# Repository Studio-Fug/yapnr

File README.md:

<p align="center">
  <picture>
    <source media="(prefers-color-scheme: dark)" srcset="branding/yapnr-logo-light.png">
    
  </picture>
</p>

<p align="center">

  <!-- Enable once the first public image (after the GHCR visibility switch) and the first
  release (v0.1.0) exist; see docs/releases.md.

  -->

</p>

# yapnr

**Yet another place and route** engine for printed circuit boards.

_The 555 flasher (a TLC555 astable blinker, 10 parts, 2 layers) from the
[regression ladder](docs/regression-ladder.md): from unplaced footprints to 100 % routed, with the
placement starts and routes it was chosen from, then the gloss pass (the copper it replaces in
red, its new copper in green), ending on KiCad's clean DRC verdict. Recorded with the opt-in
[compact placement](docs/design/compact-placement.md) and [gloss](docs/design/gloss.md)
(`PNR_COMPACT=1`, `PNR_GLOSS=1`; both off by default)._

_Left: LEDs placed freely. Right: the same chaser with its LEDs held in a
[line group](docs/constraints-and-hierarchy.md); compact placement keeps each LED's series resistor
flush beside it, and the placer moves and turns the whole row. Both with compact placement and
gloss, as above._

yapnr places components and routes copper for KiCad boards. It uses a mechanical,
Monte-Carlo-driven search: hierarchical block synthesis, power-first placement, native KiCad
routing and DRC in the loop, and electrical contracts (current, pairs, plane access) declared
next to the design.

The engine is being migrated here from the [Splanc](https://github.com/fughilli/splanc) repository,
where it was developed to lay out the Splanc Mini board. The migration plan and progress are in
[`docs/`](docs/index.md) and [`WORKLOG.md`](WORKLOG.md).
The papers and open-source projects it builds on are listed in
[Foundations and references](docs/references.md).

## Status

Alpha: this repository holds the build, CI and documentation scaffolding, a command-line stub, the
[migration plan](docs/migration-plan.md), and the engine imported from Splanc at its original
paths under `hardware/`: its committed history and its newer, uncommitted state
([manifest](docs/history/import-manifest.md)). The package restructuring follows. KiCad 10 only.

## Quick start

With [Bazelisk](https://github.com/bazelbuild/bazelisk) installed as `bazel`:

```sh
bazel run //:yapnr -- --version   # the CLI
bazel run //:doctor               # environment report
bazel test //...                  # unit tests and repository checks
bazel run //docs:build            # documentation -> docs/site/html/
```

See [DEVELOPERS.md](DEVELOPERS.md) for setup (including the headless KiCad copy on macOS) and
[CONTRIBUTING.md](CONTRIBUTING.md) for the contribution policy.

## Container image

`ghcr.io/studio-fug/yapnr` bundles KiCad 10, CPython 3.11 with CPU-only torch, and yapnr, for
linux/amd64 and linux/arm64, so running yapnr needs Docker and nothing else:

```sh
docker run --rm ghcr.io/studio-fug/yapnr:edge doctor
```

`edge` follows `main`; release tags (`X.Y.Z`, `X.Y`, `latest`) start with v0.1.0. See
[docs/containers.md](docs/containers.md) for projects, UID mapping, resource limits and Apple
Silicon, and [docs/releases.md](docs/releases.md) for versioning and releases.

## License

Copyright (C) 2026 Kevin Balke. Licensed under the GNU Affero General Public License v3.0 or later
(`AGPL-3.0-or-later`); see [LICENSE](LICENSE). Third-party material is listed in
[THIRD_PARTY.md](THIRD_PARTY.md).

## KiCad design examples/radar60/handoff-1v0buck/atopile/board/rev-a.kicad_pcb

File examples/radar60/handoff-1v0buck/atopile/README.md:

# atopile board, ERC-equivalent report, and pin mapping

Added at the request of the agent receiving this handoff: "please include the original
atopile-generated board/netlist, its schematic/ERC check report, and the symbolic-to-numeric
IC pin mapping. The current schematic checker misreads the integrated KiCad 10 board, so
those will let me verify connectivity independently." The rest of the handoff (routed boards,
documents, simulations, manifest) is described in
`../README.md`.

## `board/` -- the original atopile-generated board (parts unplaced, unrouted)

atopile writes no KiCad schematic; `rev-a.kicad_pcb` **is** the netlist (every footprint pad
carries its net name) and is the pre-place/pre-route ground truth the router's seed and every
`candidate.kicad_pcb` descend from.

- `rev-a.kicad_pcb` -- the build output (atopile 0.15.8, KiCad CLI 10.0.6; see `result.json`).
  No zone fills, 520 KB uncompressed, committed as-is.
- `ato.log` -- the full atopile build log for this output (build-design, BOM, variable-report,
  power-tree, pinout targets).
- `result.json`, `catalog.json` -- build manifest and parts catalog atopile wrote alongside the
  board, including the sha256 of every output file atopile produced (`result.json.sha256`).
- `rev-a.bom.csv` / `rev-a.bom.json` -- bill of materials (manufacturer, MPN, LCSC part #).
- `power_tree.md`, `rev-a.power_tree.ato.json`, `rev-a.variables.ato.json` -- atopile's own
  power-tree and parameter reports for this build.
- `hook.jsonl` -- atopile's module-patch trace for this run (diagnostic only).

## `pinout/` -- the symbolic-to-numeric IC pin mapping

One JSON file per fitted part (atopile's `pinout` build target), each giving, per lead:
`leadDesignator` (the symbolic pin/ball name atopile's source uses), `padNumbers` (the numeric
KiCad pad number(s) that lead maps to), `netName` (the net on `rev-a.kicad_pcb`), and
`isConnected`. This is the authoritative symbolic<->numeric bridge for every IC on the board,
including:

- U1 (`155_radio_u1.json`, IWR6843) -- 161 leads against the ABL0161 ball map.
- U2 (`086_pmic_u2.json`, LP87524J) -- 27 leads.
- U3 (`023_flash_u3.json`) -- 9 leads.
- U4 (`013_can_u4.json`) -- 9 leads.
- U5 (`093_power_in_efuse.json`, TPS259474) -- 10 leads.
- J2 (`014_debug_j2.json`) -- 36 leads.
- Every other fitted part (passives, test points, connectors, mounting holes): one file each,
  180 files total.

The companion ball map the radar flow's own checker uses for U1 is
`examples/radar60/schematic/tools/data/abl0161_ballmap.json` (already on this branch; not
duplicated here).

## `erc/` -- the ERC-equivalent check and the reproduced "misreads KiCad 10" symptom

atopile emits no schematic, so there is no KiCad ERC to run. The radar flow's own
ERC-equivalent is `examples/radar60/schematic/tools/check_schematic.py` (already on this
branch), which re-derives pin-table, power, conflict, annotation and quantified-warning checks
directly from a built/placed/routed `.kicad_pcb`'s netlist. Its own docstring states the checks
it runs; see that file for the full list.

Both reports here were produced by running that exact script, unmodified, against two boards:

- `check-atopile-board.json` -- run against `board/rev-a.kicad_pcb` (parts unplaced).
  **64 errors**, all `"<ref> (<atopile address>) pad <N> (<N>): no pin type in the check
table"`, confined to U2 (pmic.u2), U3 (flash.u3), U4 (can.u4) and U5 (power_in.efuse).
- `check-routed-s1-board.json` -- run against
  `~/yapnr-runs/fetched/20261006-mceval-5818f8/tasks/mc~s1/result/out/s1/files/candidate.kicad_pcb`
  (the routed seed s1 board; see `../results/s1`). **573 errors**: the same 64, repeated, plus
  one additional `"net : 14 push-pull outputs [...]"` error naming 14 distinct U1 pins
  (SPIB_CS_N, LVDS_TXP/M[0:1], LVDS_CLKP/M, LVDS_FRCLKP/M, RS232_TX, MCU_CLKOUT, QSPI_CS_N,
  SPI_HOST_INTR, QSPI_CLK) as if they all sat on one net literally named `""` (empty).

### The symptom, reproduced and root-caused

This is the misread the receiving agent reported. Root cause, found by reading
`check_schematic.py`'s `Fp.__init__` (checker's S-expression footprint parser):

```python
for pad in children(node, "pad"):
    net = child(pad, "net")
    self.pads.append((pad[1], net[2] if net and len(net) > 2 else ""))
```

`pad[1]` is the **numeric KiCad pad designator** (`"1"`, `"18"`, ...) -- the first field of a
KiCad `(pad "18" smd rect ...)` node. `PIN_TYPES` (the table the error names), however, is
keyed by each part's **symbolic lead name** (`"FB_B3"`, `"CS_N"`, `"TXD"`, ...), taken from the
atopile source, not from the `.kicad_pcb` file. For U1 the two happen to coincide (the IWR6843's
BGA ball designators, e.g. `"B4"`, are used as both the KiCad pad number and the ball map key),
so U1's rows pass. For U2/U3/U4/U5 (QFN/SOIC parts with sequential numeric pads) they never
coincide, so every lookup misses and the checker reports "no pin type in the check table" for
every pad on those four parts -- a false positive, not a real connectivity fault. We confirmed
KiCad 10 writes no `pinfunction` node on these pads either (`grep pinfunction rev-a.kicad_pcb`
returns nothing), so the bridge the checker would need is not even present inline in the
`.kicad_pcb`; it exists only in the side-channel `pinout/*.json` files in this directory
(`leadDesignator` -> `padNumbers`). The checker does not currently read those files. A fix would
join `PIN_TYPES` through `pinout/*.json`'s `padNumbers` instead of assuming the `.kicad_pcb` pad
number already is the symbolic name.

The second symptom (routed board only: 14 outputs collapsed onto one `""`-named net) is a
separate, additional failure specific to the _routed/placed_ `.kicad_pcb` and was not
root-caused here; it is consistent with the net-name field going missing or empty for some pads
after place-and-route on this checker's parser, which independent connectivity verification
(e.g. against `erc/` and `pinout/` here, or a from-scratch netlist extraction) should treat as
a second, distinct bug in `check_schematic.py`, not a real short.

Neither report should be read as "64 wiring errors" or "573 wiring errors" on the actual board:
both counts are entirely checker false positives from this one parsing gap, confirmed identical
in kind (same four parts, same error text) on both the unplaced atopile board and the routed
seed, and the one extra routed-board error is a second, separate parser symptom. The real
connectivity is exactly what `pinout/*.json` and `board/rev-a.kicad_pcb` state net-by-net.

## `netlist/` -- independent netlists and the atopile-vs-routed-s1 diff

These netlists come from KiCad 10.0.6, not from `check_schematic.py`, so they are an
independent connectivity reference.

| File                                           | What                                                              | How                                                                                       |
| ---------------------------------------------- | ----------------------------------------------------------------- | ----------------------------------------------------------------------------------------- |
| `rev-a.d356`, `routed-s1.d356`                 | IPC-D-356 netlist (net names truncated to 14 chars by the format) | `kicad-cli pcb export ipcd356 -o OUT BOARD`                                               |
| `rev-a.netlist.json`, `routed-s1.netlist.json` | pad-level JSON: ref, pad, pinfunction, pintype, net               | `tools/netlist_json.py BOARD OUT` (KiCad's bundled Python)                                |
| `diff-rev-a-vs-routed-s1.txt`                  | net-by-net membership comparison                                  | `python3 tools/netlist_diff.py netlist/rev-a.netlist.json netlist/routed-s1.netlist.json` |

`routed-s1` is `candidate.kicad_pcb` from campaign 20261006-mceval-5818f8, seed s1. The
original file has zone fills and is 5.4 MB, so it is not committed here. Seeds s0, s2 and s3
were not exported.

Result: all 158 atopile nets have identical pad membership on routed s1, with none renamed
and none differing. The only pad-level differences come from the RF macro v2 frame:

- atopile has a single `RFM1.gnd` pad.
- The routed board adds `RFM1.rxd0`/`txd4`, which are on `RF_RXD0`/`RF_TXD4`.
- It also adds the terminations `RT1`/`RT2`, which run from `RF_RXD0`/`RF_TXD4` to `GND`.
- It also adds the dummy loads `RL1`/`RL2`, whose pad 1 has no net.

None of the pads on either board carries a `pinfunction`, so the symbolic names exist only in
`pinout/*.json`. KiCad reports pads with no net only on FID1-3, J2, U2, U3 and U4 (plus RL1/RL2
on s1), and none on U1. That confirms the routed-board checker symptom described above is a
parser artifact, not a short.

## `netlist/`: independent netlists for every board

- **IPC-D-356** (`kicad-cli pcb export ipcd356`): `rev-a.d356` and `routed-s0..s3.d356`. The format
  cuts net names to 14 characters.
- **JSON pad netlists** (`tools/netlist_json.py`, KiCad's headless Python): `rev-a.netlist.json` and
  `routed-s0..s3.netlist.json`, giving ref, pad, pin function, pin type and net per pad.
- **`diff-rev-a-vs-routed-sN.txt`** (`tools/netlist_diff.py`): on every seed, all 158 atopile nets
  have exactly the same pads on the routed board. The only differences are the RF macro v2 frame
  additions:
  - the atopile board has a single `RFM1.gnd` pad;
  - the routed boards add `RFM1.rxd0` and `RFM1.txd4`, the terminations `RT1`/`RT2`
    (`RF_RXD0`/`RF_TXD4` to `GND`), and the dummy loads `RL1`/`RL2`, whose pad 1 has no net.

## `pin-tables/`: symbolic lead to pad to net, per IC

`tools/pin_tables.py` writes one table per part (`U1`–`U6`, `J1`–`J3`, `Y1`, `Q1`, `D1`–`D3`, as
`.md` and `.csv`). Each row gives:

- the atopile lead name;
- its pad or ball;
- the net in atopile's pinout;
- the net on the atopile board;
- the net on each routed seed.

`INDEX.md` counts the rows where any board net differs from the pinout. **That count is 0 for every
part**, so connectivity agrees symbol by symbol.

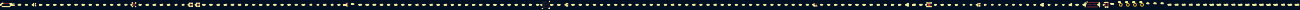
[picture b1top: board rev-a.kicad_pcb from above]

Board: 2 copper layers, 183 parts (0 on the bottom side), 102 nets, no tracks yet.

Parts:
C1, C2, C3, C4, C5, C6, C26, C27, C28, C29, C30, C31, C32, C34, C35, C37, C38, C39, C40, C43, C44, C45, C46, C47, C48, C49, C50, C51, C54, C57, C60, C61, C62, C63, C64, C65, C66, C67, C68, C70, C71, C72: C_0402_1005Metric
C7, C9, C11, C12, C13, C14, C15, C16, C17, C18, C19, C20, C21, C22, C24, C33, C36, C53, C56, C59: C_0805_2012Metric
C8, C10, C23, C25, C41, C42, C52, C55, C58, C69: C_0603_1608Metric
D1: SOT-23
D2: SOT-323_SC-70
D3: D_SMF
D4: LED_0603_1608Metric
FB1, FB2, FB3, FB4, FB5: L_0805_2012Metric
FID1, FID2, FID3: Fiducial_1mm_Mask2mm
J1: JST_GH_SM08B-GHS-TB_1x08-1MP_P1.25mm_Horizontal
J2: Samtec_QTH-030-01-L-D-A_2x30_P0.5mm_Vertical
J3: PinHeader_2x05_P1.27mm_Vertical_SMD
L1, L2: L_0805_2012Metric
L3, L4: L_Vishay_IHLP-1616
MH1, MH2, MH3, MH4: MountingHole_2.7mm_M2.5_Pad
Q1: SOT-23
R1, R2, R3, R4, R5, R6, R7, R8, R9, R10, R11, R12, R13, R14, R15, R16, R17, R18, R19, R20, R21, R22, R23, R24, R25, R26, R27, R28, R29, R30, R31, R32, R33, R34, R35, R36, R37, R38, R39, R40, R41, R42, R43, R44, R45, R46, R47, R48, R49, R50, R51, R52, R53, R54, R55, R56, R57, R58: R_0402_1005Metric
RFM1: Radar60_RFM1_Placeholder
R_SH1: Vishay_WFCP0612_1632Metric
TP1: Radar60_KelvinSense_2Pad_P1.27mm
TP2, TP3, TP4, TP5, TP6, TP7, TP8, TP9, TP10, TP11, TP12, TP13, TP14, TP15, TP16, TP17, TP18, TP19, TP20: TestPoint_Pad_D1.0mm
U1: TI_ABL0161B_FCBGA-161_10.4x10.4mm_Layout15x15_P0.65mm
U2: TI_RNF0026C_VQFN-HR-26_4.5x4mm_P0.5mm
U3: WSON-8-1EP_6x5mm_P1.27mm_EP3.4x4mm
U4: Texas_DRB0008A
U5: TI_RPW0010A_VQFN-HR-10_2x2mm_P0.45mm
U6: SOT-23-6
Y1: Crystal_SMD_3225-4Pin_3.2x2.5mm

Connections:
1V0_BUCK: C20.1, L3.2, R22.2, R_SH1.1, TP1.1
1V0_PA: C52.1, C53.1, C54.1, R46.2, TP2.1, U1.A2, U1.B2
1V0_RF1: C22.1, C23.1, C55.1, C56.1, C57.1, FB3.2, R16.1, U1.G5, U1.H5, U1.J5
1V0_RF2: C24.1, C25.1, C58.1, C59.1, C60.1, FB4.2, FB5.2, R17.1, R23.2, R46.1, U1.C2, U1.D2
1V0_SH: FB3.1, FB4.1, FB5.1, R_SH1.2, TP1.2
1V2: C7.1, C8.1, C45.1, C46.1, C47.1, C48.1, C49.1, C50.1, C61.1, C70.1, FB1.2, TP3.1, U1.G15, U1.H15, U1.N11, U1.P14, U1.P15, U1.R6
1V2_BUCK: C19.1, FB1.1, L2.2, U2.14
1V8: C9.1, C10.1, C39.1, C40.1, C41.1, C42.1, C43.1, C44.1, C51.1, C64.1, FB2.2, R15.1, TP4.1, U1.B11, U1.B12, U1.D15, U1.F5, U1.K5, U1.R9
1V8_BUCK: C21.1, FB2.1, L4.2, U2.21
3V3: C18.1, L1.2, R54.1, R55.1, U2.8, U6.1
3V3_RADIO_IO: C4.1, C5.1, C6.1, C65.1, C66.1, C67.1, C68.1, C69.1, J3.1, R10.1, R11.1, R12.1, R25.1, R26.1, R28.1, R29.1, R43.2, R44.1, R45.1, R48.1, R51.1, R53.1, R54.2, R56.1, TP5.1, U1.F15, U1.R10, U3.8, U4.5, U6.6
5V_SYS: C2.1, C3.1, C14.1, C15.1, C16.1, C17.1, C31.1, C36.1, C37.1, R19.1, R20.1, R21.1, R39.1, R40.1, TP6.1, U2.9, U2.13, U2.18, U2.22, U2.26, U4.3, U5.6
CANH: D1.1, J1.5, R4.1, U4.7
CANL: D1.2, J1.6, R5.2, U4.6
CAN_RX: R2.2, U1.F14
CAN_RXD: R1.1, R2.1, U4.4
CAN_TERM_MID: C1.1, R4.2, R5.1
CAN_TX: R7.1, U1.H14
CAN_TXD: R6.2, R7.2, U4.1
DAMP_1V0_RF1: C12.1, R16.2
DAMP_1V0_RF2: C13.1, R17.2
DAMP_1V8: C11.1, R15.2
DCA_RST_N: J2.59, R8.1
EFUSE_DVDT: C32.1, U5.7
EFUSE_EN_UVLO: R41.1, R42.2, U5.1
EFUSE_ILM: R34.1, U5.9
EFUSE_ITIMER: C35.1, U5.10
EFUSE_OVLO: R35.1, R36.2, U5.2
EFUSE_PG: R38.1, R39.2, TP7.1, U2.20, U5.3
EFUSE_PGTH: R37.1, R40.2, U5.4
FRAME_START: TP8.1, U1.N8
GND: C1.2, C2.2, C3.2, C4.2, C5.2, C6.2, C7.2, C8.2, C9.2, C10.2, C11.2, C12.2, C13.2, C14.2, C15.2, C16.2, C17.2, C18.2, C19.2, C20.2, C21.2, C22.2, C23.2, C24.2, C25.2, C26.2, C27.2, C28.2, C29.2, C30.2, C31.2, C32.2, C33.2, C34.2, C35.2, C36.2, C37.2, C38.2, C39.2, C40.2, C41.2, C42.2, C43.2, C44.2, C45.2, C46.2, C47.2, C48.2, C49.2, C50.2, C51.2, C52.2, C53.2, C54.2, C55.2, C56.2, C57.2, C58.2, C59.2, C60.2, C61.2, C62.2, C63.2, C64.2, C65.2, C66.2, C67.2, C68.2, C69.2, C70.2, C71.2, C72.2, D1.3, D2.3, D3.2, J1.3, J1.4, J1.MP, J2.18, J2.24, J2.30, J2.36, J2.42, J2.48, J2.54, J2.60, J2.MP1, J2.MP2, J2.MP3, J2.MP4, J3.3, J3.5, J3.9, MH1.1, MH2.1, MH3.1, MH4.1, Q1.2, R3.2, R13.2, R18.2, R34.2, R35.2, R37.2, R38.2, R41.2, R49.2, R50.2, R52.2, RFM1.gnd, TP9.1, TP10.1, U1.A1, U1.A3, U1.A5, U1.A7, U1.A9, U1.A13, U1.A15, U1.B1, U1.B3, U1.B5, U1.B7, U1.B9, U1.B14, U1.C1, U1.C3, U1.C4, U1.C5, U1.C6, U1.C7, U1.C8, U1.C9, U1.C14, U1.E1, U1.E2, U1.E3, U1.E5, U1.E6, U1.E8, U1.E10, U1.E11, U1.F3, U1.F9, U1.F11, U1.G1, U1.G2, U1.G3, U1.G6, U1.G7, U1.G8, U1.G10, U1.H3, U1.H7, U1.H9, U1.H11, U1.J1, U1.J2, U1.J3, U1.J6, U1.J7, U1.J8, U1.J10, U1.K3, U1.K7, U1.K8, U1.K9, U1.K10, U1.K11, U1.L1, U1.L2, U1.L3, U1.L5, U1.L6, U1.L8, U1.L10, U1.M3, U1.N1, U1.N2, U1.N3, U1.R1, U1.R15, U2.4, U2.11, U2.17, U2.24, U2.27, U3.4, U3.9, U4.2, U4.9, U5.8, U6.2, Y1.2, Y1.4
I2C_SCL: J2.53, R28.2, U1.G14, U2.5
I2C_SDA: J2.51, R29.2, U1.F13, U2.6
JTAG_TCK: J3.4, U1.P10
JTAG_TDI: J3.8, U1.R11
JTAG_TMS: J3.2, U1.N10
LVDS_CLK_N: J2.46, U1.L15
LVDS_CLK_P: J2.44, U1.L14
LVDS_FRCLK_N: J2.28, U1.M15
LVDS_FRCLK_P: J2.26, U1.M14
LVDS_TX0_N: J2.58, U1.J15
LVDS_TX0_P: J2.56, U1.J14
LVDS_TX1_N: J2.52, U1.K15
LVDS_TX1_P: J2.50, U1.K14
NERROR_IN: R44.2, U1.N7
NERROR_OUT: Q1.1, R45.2, TP11.1, U1.N6
NRESET: C26.1, J3.10, R8.2, R27.2, TP12.1, U1.R3
PMIC_EN2_GPIO2: R20.2, R24.1, U2.15
PMIC_FB_B2: R22.1, R23.1, U2.1
PMIC_NINT: R25.2, R47.1, TP14.1, U2.19
PMIC_PGOOD: J2.13, R26.2, R27.1, TP13.1, U2.16
PMIC_SW_B0: L1.1, R30.1, U2.10
PMIC_SW_B1: L2.1, R31.1, U2.12
PMIC_SW_B2: L3.1, R32.1, U2.25
PMIC_SW_B3: L4.1, R33.1, U2.23
QSPI_CLK: R9.1, U1.R12
QSPI_CLK_FLASH: R9.2, U3.6
QSPI_CS_N: R10.2, U1.P11, U3.1
QSPI_D0: U1.R13, U3.5
QSPI_D1: U1.N12, U3.2
QSPI_D2: R11.2, U1.R14, U3.3
QSPI_D3: R12.2, U1.P12, U3.7
RADIO_GPIO_2: R47.2, U1.K13
RF_RX1: RFM1.rx1, U1.M2
RF_RX2: RFM1.rx2, U1.K2
RF_RX3: RFM1.rx3, U1.H2
RF_RX4: RFM1.rx4, U1.F2
RF_TX1: RFM1.tx1, U1.B4
RF_TX2: RFM1.tx2, U1.B6
RF_TX3: RFM1.tx3, U1.B8
SOP0_TDO: J3.6, R48.2, TP15.1, U1.N13
SOP1: R49.1, TP16.1, U1.G13
SOP2_PMIC_CLKOUT: R14.2, R50.1, TP17.1, U1.P9
SPIA_CLK: J2.9, U1.E13
SPIA_CS_N: J2.7, R51.2, U1.E15
SPIA_MISO: J2.12, R6.1, U1.E14
SPIA_MOSI: J2.11, R1.2, U1.D13
SPI_HOST_INTR: J2.10, U1.P13
STB: R3.1, U4.8
SYNC_IN: R52.1, U1.P4
UART_RX: J2.55, R53.2, R57.1, TP18.1, U1.N4
UART_RX_J1: D2.2, J1.8, R57.2
UART_TX: J2.57, R58.1, TP19.1, U1.N5
UART_TX_J1: D2.1, J1.7, R58.2
VBGAP: C63.1, U1.B10
VIN_5V: C33.1, C34.1, D3.1, J1.1, J1.2, R36.1, R42.1, U5.5
VIO_LS_ON: R24.2, R55.2, U6.3
VOUT_14APLL: C38.1, U1.A10
VOUT_14SYNTH: C62.1, U1.B13
WARM_RESET: R56.2, TP20.1, U1.N9
XTAL_N: C71.1, U1.C15, Y1.3
XTAL_P: C72.1, U1.B15, Y1.1
led_a: D4.2, R43.1
led_k: D4.1, Q1.3
pmic-1: R13.1, R14.1, U2.3
pmic-1-1: R18.1, R19.2, U2.7
pmic-2: R21.2, U2.2
snb0: C27.1, R30.2
snb1: C28.1, R31.2
snb2: C29.1, R32.2
snb3: C30.1, R33.2

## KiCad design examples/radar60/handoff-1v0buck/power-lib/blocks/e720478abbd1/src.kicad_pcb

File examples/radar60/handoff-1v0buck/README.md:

# radar60 handoff: the 1.0 V buck pass (throwaway branch)

This bundle hands radar60 Rev A to another agent so they can finish the board and rerun the VnV
independently. It is **not** for merging. The branch `claude/radar60-1v0buck-handoff` is
`claude/radar60-models` (`d6ad8080`) plus this directory, plus one change to
`examples/radar60/schematic/elec/src/radar60.ato` (the LVDS uncoupled-length annotations, see
below).

The content commit's SHA is under "Commits" at the end.

## State in one paragraph

U2's buck stage has a 1.0 V leg resistance budget of 0.5 mΩ. It meets that at 0.383 mΩ on every
routed seed, using the hybrid power-block library: U2 block `34c7ed35931c` and U5 block
`de5bfabb679f`. The board is **not** complete:

- 148–162 pads are still unconnected;
- DRC finds 14 violations plus 6–11 that KiCad ignores by default, including one short on s0;
- LVDS has 0–1 of 8 legs connected and QSPI 4–6 of 7;
- most rails other than 1V0_BUCK are still open.

The RF macro v2 copper is identical on every seed (digest equal; rf_audit A1–A6 pass). ANT-02 has
preregistered misses and D14 (the PA-feed coupling) is open: see `docs/rf-status.md`.

## Where everything is

| Path                                                     | What                                                                                                                                                                                                                                                                                                                            |
| -------------------------------------------------------- | ------------------------------------------------------------------------------------------------------------------------------------------------------------------------------------------------------------------------------------------------------------------------------------------------------------------------------- |
| `results/sN/` (s0–s3)                                    | One routed seed from campaign `20261006-mceval-5818f8`. Contents below.                                                                                                                                                                                                                                                         |
| `results/sN/candidate.kicad_pcb.xz`                      | The routed board. Zone fills are stripped to fit the repo's 600 KB file limit; `--refill-zones` or pcbnew restores them. The other files in this directory sit beside the board.                                                                                                                                                |
| `results/sN/candidate.kicad_pro`, `candidate.kicad_dru`  | The project and custom rules. These are the seed's; the task's route directory was not collected.                                                                                                                                                                                                                               |
| `results/sN/fp-lib-table`, `footprint-libs/`             | The footprint libraries, extracted from the board by `pnr.library_table`, which is what `integrate.py finish` runs. The table uses `${KIPRJMOD}`.                                                                                                                                                                               |
| `results/sN/placement.json`                              | The placement, rebuilt from the board (`tools/placement_from_board.py`)                                                                                                                                                                                                                                                         |
| `results/sN/out/sN/files/measure.json`                   | **The flow's full check report** (`integrate.py check` on GCP): DRC by type plus the checks KiCad ignores by default, unconnected nets, IR per rail, LVDS, QSPI, R1 macro digest, R4 foreign copper, rf_audit on the routed board                                                                                               |
| `results/sN/out/sN/files/route-diag.json`, `result.json` | The routing report and the task verdict                                                                                                                                                                                                                                                                                         |
| `results/sN/drc/drc-fresh-local.json`                    | An independent local KiCad DRC of the restored board, refilled, all severities, with the footprint libraries                                                                                                                                                                                                                    |
| `results/sN/drc/fill-strip-equivalence.json`             | Proof that stripping the fills changed nothing: DRC by type and unconnected count are equal for the original and the stripped board                                                                                                                                                                                             |
| `results/sN/logs/`                                       | The step logs (place, select, finish, route, check). Paths in them are container paths.                                                                                                                                                                                                                                         |
| `results/sN/record.json`                                 | The task record: image digest, machine, timings                                                                                                                                                                                                                                                                                 |
| `results/dataset.jsonl`                                  | The campaign's assembled dataset                                                                                                                                                                                                                                                                                                |
| `power-lib/`                                             | The power-block library. **U2 `34c7ed35931c` and U5 `de5bfabb679f` are preserved**, along with the runners-up `a24fb2995477` and `e720478abbd1`.                                                                                                                                                                                |
| `seed/`                                                  | The prepared work directory the four seeds ran from (`source`, `fixblocks`, `prepare`), including the routing constraints (`constraints-place.yaml`, `inputs/rules.json`, `inputs/rules0.json`, `inputs/graph*.json`)                                                                                                           |
| `explore_jobs_w4b.toml`                                  | The GCP campaign definition (live view on)                                                                                                                                                                                                                                                                                      |
| `atopile/`                                               | The original atopile board (`board/rev-a.kicad_pcb`) and its build outputs, plus: IPC-D-356 and JSON netlists of the atopile board and every seed with their diffs, the per-IC pin tables (symbolic lead, pad, net), the ERC-equivalent reports, and the root cause of the schematic checker's misreading (`atopile/README.md`) |
| `docs/`                                                  | The design objectives and acceptance documents (requirements, board design with decisions D0–D15, calculations, stage 3b RF and board, stage 3c plan and consolidation report), plus `vnv-matrix.md`, `lvds-uncoupled-resolution.md`, `rf-status.md` and `simulations.md`. `docs/INDEX.md` maps each to its source.             |
| `sims/`                                                  | EM inputs and configs (openEMS models and job files, campaign plans, generator variants), S-parameters and summaries of the final campaigns, and the Palace status (`docs/simulations.md`)                                                                                                                                      |
| `MANIFEST.md`, `manifest.json`                           | Engine/source SHAs, image digests, tool versions, environment, commands, and the sha256 of every file                                                                                                                                                                                                                           |
| `localize.py`                                            | Unpacks the bundle: decompresses `.gz` and `.xz` and fills in `${HANDOFF}`/`${REPO}`                                                                                                                                                                                                                                            |
| `tools/`                                                 | `placement_from_board.py`, `hash_bundle.py` (the netlist and pin-table tools are in `atopile/tools/`)                                                                                                                                                                                                                           |

## Results per seed (from each `measure.json`)

| Seed | Unconnected | DRC (+ ignored by default)             | 1V0_BUCK      | Other rails                                                    | LVDS legs | QSPI |
| ---- | ----------- | -------------------------------------- | ------------- | -------------------------------------------------------------- | --------- | ---- |
| s0   | 152         | 14 (+10), including 1 `shorting_items` | 0.383 mΩ pass | 3V3_RADIO_IO pass; the rest open                               | 0/8       | 4/7  |
| s1   | 148         | 14 (+7)                                | 0.383 mΩ pass | 1V8 pass (14.6 mΩ); the rest open                              | 0/8       | 4/7  |
| s2   | 162         | 14 (+6)                                | 0.383 mΩ pass | 1V8 pass; the rest open                                        | 1/8       | 6/7  |
| s3   | 153         | 14 (+11)                               | 0.383 mΩ pass | 1V0_RF1 fails (8.4 mΩ vs 4); 3V3_RADIO_IO fails; the rest open | 0/8       | 4/7  |

**Independent re-check:**

- **s0, s2 and s3:** a fresh local KiCad DRC of the restored board (fills restored, footprint
  libraries present) gives exactly the GCP check's DRC types, counts and unconnected count.
- **s1 (open discrepancy):** the fresh run finds 11 violations, not 14. The 3 `items_not_allowed`
  the GCP check reported don't reproduce with the seed's project and design rules, while unconnected
  (148) matches. The likely cause is a difference between the task's route-directory project/DRU and
  the seed's, but it is not confirmed.

## What still fails, and what hasn't been run

**Board (the acceptance gates are in `docs/vnv-matrix.md` and `docs/stage3c/plan.md`):**

1. **Unconnected pads (148–162) and DRC.** Includes s0's short and the rise from 9 to 14 since wave
   4: dangling vias, isolated copper, and one QSPI length over 25 mm.
2. **IR.** Every rail except 1V0_BUCK (and 1V8/3V3_RADIO_IO on some seeds) is open or failing.
3. **LVDS 0–1/8.** The placement leaves no coupled channel; the fix is a re-place that keeps pair
   ends adjacent. The acceptance limit is ≤ 3 mm uncoupled, see `docs/lvds-uncoupled-resolution.md`.
4. **`power_block.py` ranking.** It must put any block whose own IR path is open below every block
   without one. Fix that before re-making the library.
5. **PA-feed integration.**
   - `merge_macro` accepts `RFM1_PA_FEED` but drops its copper;
   - still needed: the through vias, A2/B2 as skipped pads, and the In3 1V0 pour;
   - `finish`'s pre-route R1 check needs narrowing;
   - U1 GND ball vias are needed for D14.
6. **`route`'s internal `fixed_copper --validate` failure** on the old arm-A placement. Its stderr
   is swallowed.

**RF (`docs/rf-status.md`, `docs/simulations.md`):**

- ANT-02: RL −7.2 dB against −10 dB, gain at 60.3 GHz and efficiency; all preregistered misses.
- D14: TX1 −33.5 dB against −40 dB, open.
- **Not run:**
  - C2 (RF sign-off on routed copper);
  - D14 on routed copper with U1 GND vias;
  - c1b-6 at 15 µm and the Dk corners;
  - the D12 brackets;
  - embedded patterns.

**Not included:**

- the routed boards' zone fills (restored by refill);
- the task route directories' own project/DRU/fp-lib-table and `selection.json` (the campaign didn't
  collect them; `placement.json` is rebuilt from the board);
- EM field dumps, meshes and Palace validation runs (rebuild by rerunning the campaigns);
- the TI-EVM extraction script and any TI file (never committed);
- the owner's cloud config and credentials.

**Proprietary or private dependencies:** none for verification. The openEMS and Palace images
live in the owner's private registry; rebuild them from `docker/` (`docs/simulations.md`).

## How to run

```sh
python3 examples/radar60/handoff-1v0buck/localize.py /path/to/handoff
```

Then follow `MANIFEST.md` (DRC, netlists, pin tables, the flow from the seed, the GCP campaign, EM).

Use KiCad 10's **headless** copy for `kicad-cli` and KiCad's Python. The review run behind the
hybrid
library used the GUI app's Python and Homebrew's `kicad-cli`, which this project does not allow.

## LVDS uncoupled length

The 1 mm vs 3 mm conflict is resolved to **3 mm**; `docs/lvds-uncoupled-resolution.md` has the
evidence. On this
branch the four `@pnr-pair` annotations in `radar60.ato` now say 3.0, matching the DRU and
constraints. The routed results were
produced under the DRU's 3 mm, so nothing changes for them.

## Commits

- Content commit: `56d1d37a2fec650659dfb62020170b3fba92f2c6`
  (this README is updated in the following commit).

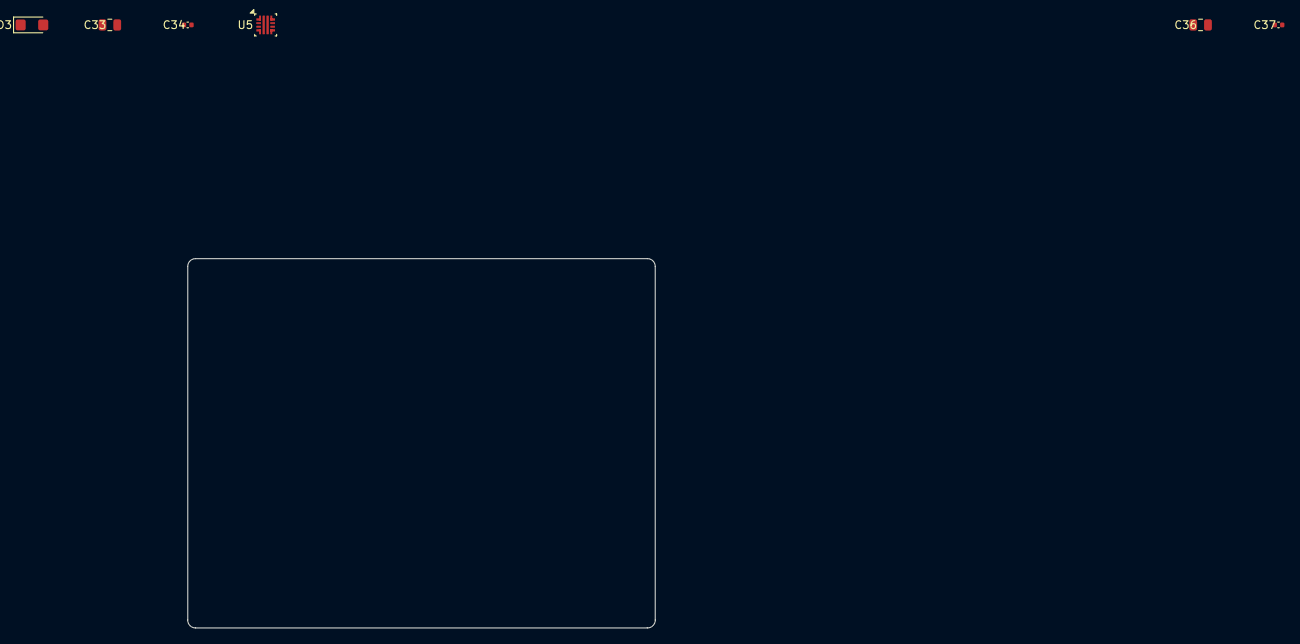
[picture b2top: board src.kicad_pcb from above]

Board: 6 copper layers, 60.0 x 47.4 mm, 6 parts (0 on the bottom side), 3 nets, no tracks yet.

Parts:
C33, C36: C_0805_2012Metric
C34, C37: C_0402_1005Metric
D3: D_SMF
U5: TI_RPW0010A_VQFN-HR-10_2x2mm_P0.45mm

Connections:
5V_SYS: C36.1, C37.1, U5.6
GND: C33.2, C34.2, C36.2, C37.2, D3.2, U5.8
VIN_5V: C33.1, C34.1, D3.1, U5.5

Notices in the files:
README.md:
<img src="https://img.shields.io/badge/license-AGPL--3.0--or--later-blue.svg"
alt="License: AGPL-3.0-or-later">
